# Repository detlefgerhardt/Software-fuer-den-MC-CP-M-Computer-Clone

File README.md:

# Software und Zubehör für den MC CP/M-Computer-Clone

**Dieses Repository befindet sich noch im Aufbau. Die Programme sind teilweise noch unvollständig und ungetestet!**

Dieses Repository enthält vollständig überarbeite Software (Monitor, BIOS und Tools) für den MC CP/M Computer Nachbau von Ulrich Haumann. Die Software basiert sowohl auf der Originalsoftware von Rolf-Dieter Klein als auch auf Änderungen und neuen Programmen von Ulrich Haumann.

**https://github.com/uli-pi/MC-CPM-Computer-Clone**

Zusätzlich findet man hier 3D-Druckteile und Adapter für den Einbau des Computers in ein 19" Systemgehäuse oder Baugruppenträger.

Ziel dieses Repositories hier ist es, die Software des MC CP/M Computer-Clones möglichst gut zu dokumentieren und weiter zu entwickeln.
Der Monitor soll kompatibel bleiben und die Kompatibilität des BIOS ist von CP/M vorgegeben. Teile des Monitors und des BIOS, die nicht für CP/M benötigt werden, wurden bereits weitgehend entfernt.

Geplante Erweiterungen:
- Optimierung, unnötige Routinen entfernen (im BIOS weitgehend erledigt, im Monitor ist noch einiges zu tun)
- Unterstützung weiterer Diskettenformate und eine einfacher Implementierung neuer Formate (weitgehend erledigt inkl. der dynmaischen Umkonfiguration der Laufwerksdaten zur Laufzweit (inzwischen implementiert und im Test)
- Die Hardwareunterstützung auf die aktuelle Hardware des MC CP/M-Clones reduzieren, um die Software zu vereinfachen. Wer erweiterte Kompatibilität benötigt, kann auf die Originalsoftware zurückgreifen).
- Unterstützung der IDE/CF-Karte gleichzeitig zusammen mit Diskettenlaufwerken (erledigt)
- Vereinheitlichung der Tools - zum Beispiel für die Nutzung von Disketten und IDE/CF-Laufwerke (hier kann noch weiter optimiert werden. Bisher gibt es noch eigene Tools zum Einrichten von IDE/CF-Laufwerken)

Dieses Repository enthält folgende Teilprojekte (noch in Arbeit, Liste nicht immer aktuell):
- **NMON** - der Monitor für den MC CP/M-Computer, geändert und erweitert, basierendem auf dem Original-Monitor von Rolf-Dieter Klein und einigen Anpassungen von Ulrich Haumann
- **NBIOS** - das angepasste BIOS, die Schnittstelle zwischen dem Monitor, der Hardware und CP/M (ebenfalls basierenden auf dem Original-BIOS von RDK)
- **NBIOS-CF** - angepasstes BIOS und Tools für das IDE/CF-Interface
- **NFORM** ist das originale in Z80 geschrieben Formatierprogramm für den MC CP/M-Computer. Da es lediglich den Monitor vorrausetzt, kann es ohne CP/M und BIOS direkt im Monitor ausgeführt werden.
- **MI-C** - in MI-C programmierte Programme und Tools, um Teil abgestimmt auf das NBIOS und nur mit diesem lauffähig
- **DEV-Tools** - Entwicklungstools für CP/M und Windows (Assembler, MI-C-Compiler, eigene Tools)
- **CPM-Standardsoftware** - Standard CP/M-Programme, die für Entwicklung und die Systemeinrichtung benötigt werde oder nützlich sind.
- **VT100-Animationen** - Ausgewählte VT100-Animationen inkl. Anzeige-Tools. Die Anzeige-Tools korrigieren nötigenfalls die Zeilenendezeichen und können auf Wunsch alle Dateien auf einem Laufwerk in zufälliger Reihenfolge ausgeben.

Zum Thema Gehäuse und 3D-Druck (neu):
- **Gehäuse und 3D-Druck** enthält Teile wie Fronplatten oder Laufwerkskäfige (Halterungen) für den Einbau in 19" Gehäuse und Baugruppenträger.
- **KiCAD** enthält derzeit Adapter-Platinen, die den Anschluss von Diskettenlaufwerken erleichtern.

Achtung. Die Versionierung und die Namen der Dateien wurden gegenüber den Originalen geändert, um eine klaren Schnitt zwischen der Originalsoftare und den Programmen dieses Projektes zu haben und Verwechselungen zu vermeiden.

Das CP/M wurde auf ein 58K-System geändert. Das CP/M beginnt bei Adresse CC00h und das BIOS bei Adresse E200h. Das war notwendig um ausreichend Platz für BIOS-Erweiterung, Debuggung und Experimente zu schaffen.

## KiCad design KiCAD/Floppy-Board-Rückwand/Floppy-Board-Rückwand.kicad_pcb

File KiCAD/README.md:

# Adapter-Platinen für den Gehäuseeinbau bzw. den einfacheren Anschluss von Laufwerken

* Der **MC_CPM_Floppyadapter** ist ein kleine Platine, mit dem man bis zu vier 3 1/2" Laufwerke ohne gedrehtes Kabel am FLO-Controller des MC CP/M-Computer betreiben kann. Auch gemischt mit 5 1/4" Laufwerken.

* **Floppy-Board-Rückwand** ist eine Platine, die den 34 und der 50-poligen Floppy-Anschluss auf der Rückseite eines Systemgehäuses herausführt. Ein passende Halterung findet man im Order 3D-Druck.

Bei Gelegenheit werde ich die Projekte umbenennen und sinnvolle Namen vergeben. ;-)

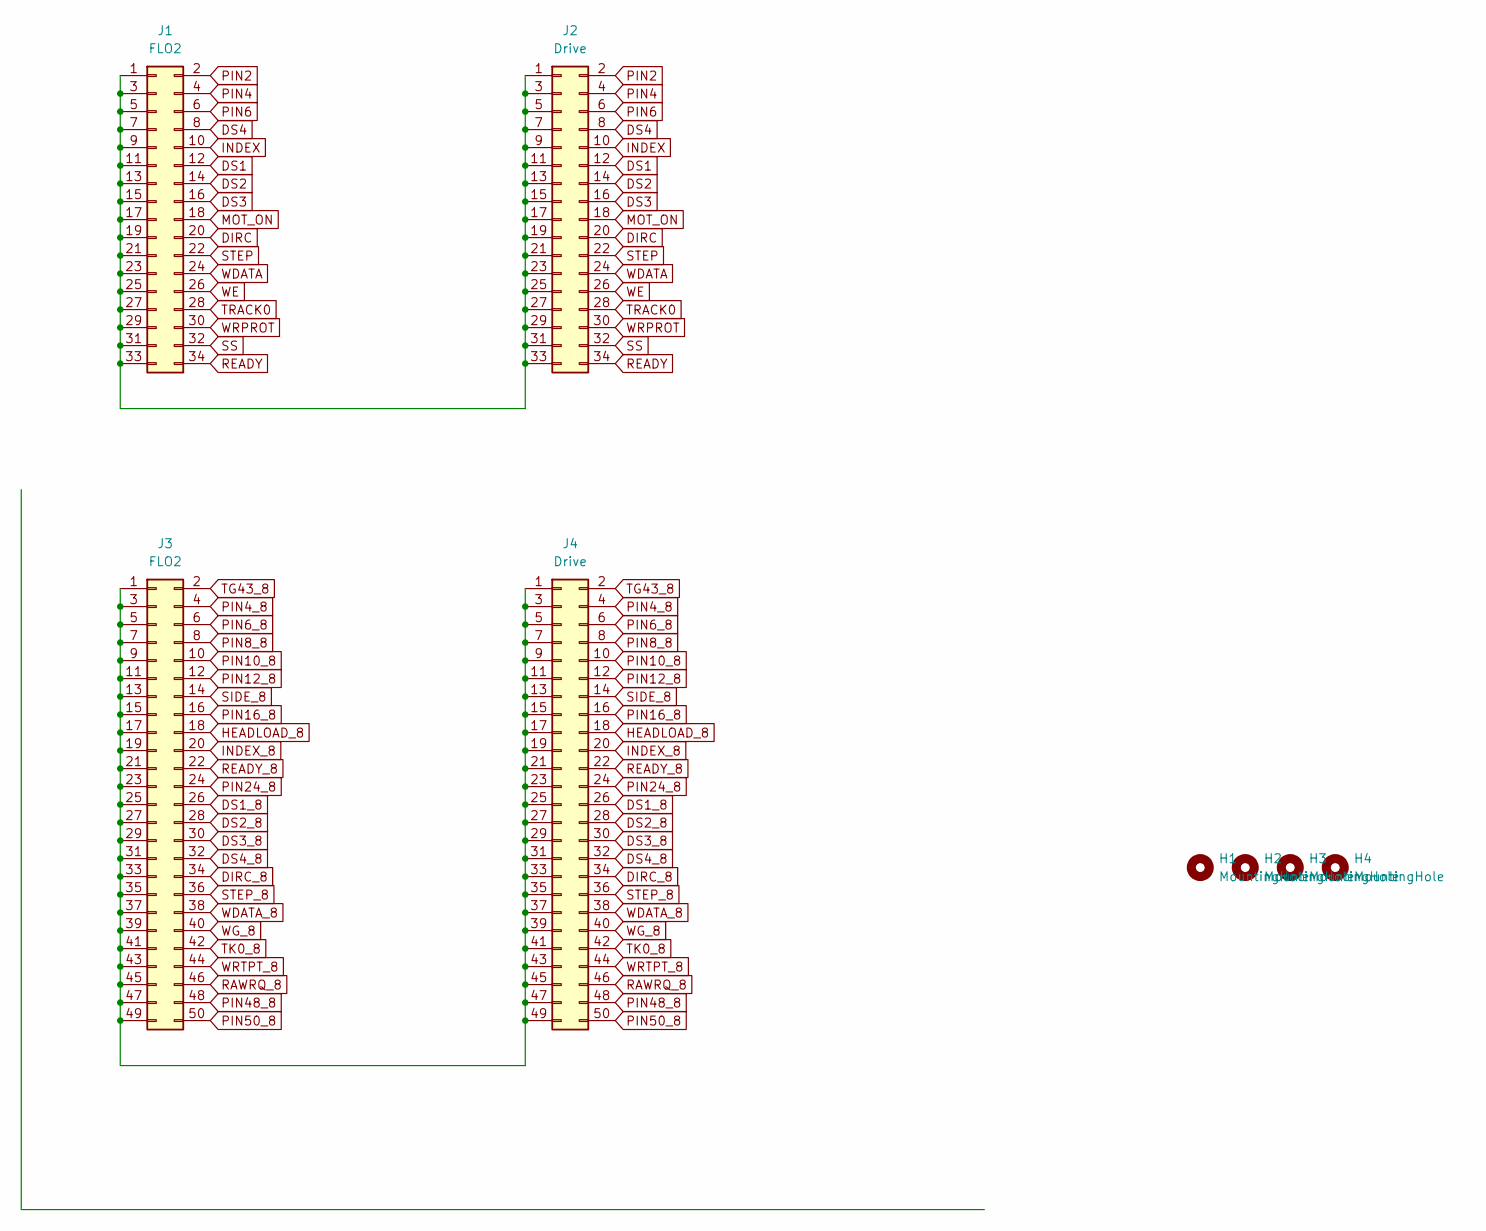
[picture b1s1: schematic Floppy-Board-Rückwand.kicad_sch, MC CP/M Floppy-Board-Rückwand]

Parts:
H1, H2, H3, H4: MountingHole; MountingHole_3.2mm_M3
J1: FLO2; PinSocket_2x17_P2.54mm_Vertical
J2: Drive; PinSocket_2x17_P2.54mm_Vertical
J3: FLO2; PinSocket_2x25_P2.54mm_Vertical
J4: Drive; PinSocket_2x25_P2.54mm_Vertical

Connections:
DIRC: J1.20, J2.20
DIRC_8: J3.34, J4.34
DS1: J1.12, J2.12
DS1_8: J3.26, J4.26
DS2: J1.14, J2.14
DS2_8: J3.28, J4.28
DS3: J1.16, J2.16
DS3_8: J3.30, J4.30
DS4: J1.8, J2.8
DS4_8: J3.32, J4.32
HEADLOAD_8: J3.18, J4.18
INDEX: J1.10, J2.10
INDEX_8: J3.20, J4.20
MOT_ON: J1.18, J2.18
unnamed: J1.1, J1.3, J1.5, J1.7, J1.9, J1.11, J1.13, J1.15, J1.17, J1.19, J1.21, J1.23, J1.25, J1.27, J1.29, J1.31, J1.33, J2.1, J2.3, J2.5, J2.7, J2.9, J2.11, J2.13, J2.15, J2.17, J2.19, J2.21, J2.23, J2.25, J2.27, J2.29, J2.31, J2.33
unnamed: J3.1, J3.3, J3.5, J3.7, J3.9, J3.11, J3.13, J3.15, J3.17, J3.19, J3.21, J3.23, J3.25, J3.27, J3.29, J3.31, J3.33, J3.35, J3.37, J3.39, J3.41, J3.43, J3.45, J3.47, J3.49, J4.1, J4.3, J4.5, J4.7, J4.9, J4.11, J4.13, J4.15, J4.17, J4.19, J4.21, J4.23, J4.25, J4.27, J4.29, J4.31, J4.33, J4.35, J4.37, J4.39, J4.41, J4.43, J4.45, J4.47, J4.49
PIN2: J1.2, J2.2
PIN4: J1.4, J2.4
PIN4_8: J3.4, J4.4
PIN6: J1.6, J2.6
PIN6_8: J3.6, J4.6
PIN8_8: J3.8, J4.8
PIN10_8: J3.10, J4.10
PIN12_8: J3.12, J4.12
PIN16_8: J3.16, J4.16
PIN24_8: J3.24, J4.24
PIN48_8: J3.48, J4.48
PIN50_8: J3.50, J4.50
RAWRQ_8: J3.46, J4.46
READY: J1.34, J2.34
READY_8: J3.22, J4.22
SIDE_8: J3.14, J4.14
SS: J1.32, J2.32
STEP: J1.22, J2.22
STEP_8: J3.36, J4.36
TG43_8: J3.2, J4.2
TK0_8: J3.42, J4.42
TRACK0: J1.28, J2.28
WDATA: J1.24, J2.24
WDATA_8: J3.38, J4.38
WE: J1.26, J2.26
WG_8: J3.40, J4.40
WRPROT: J1.30, J2.30
WRTPT_8: J3.44, J4.44

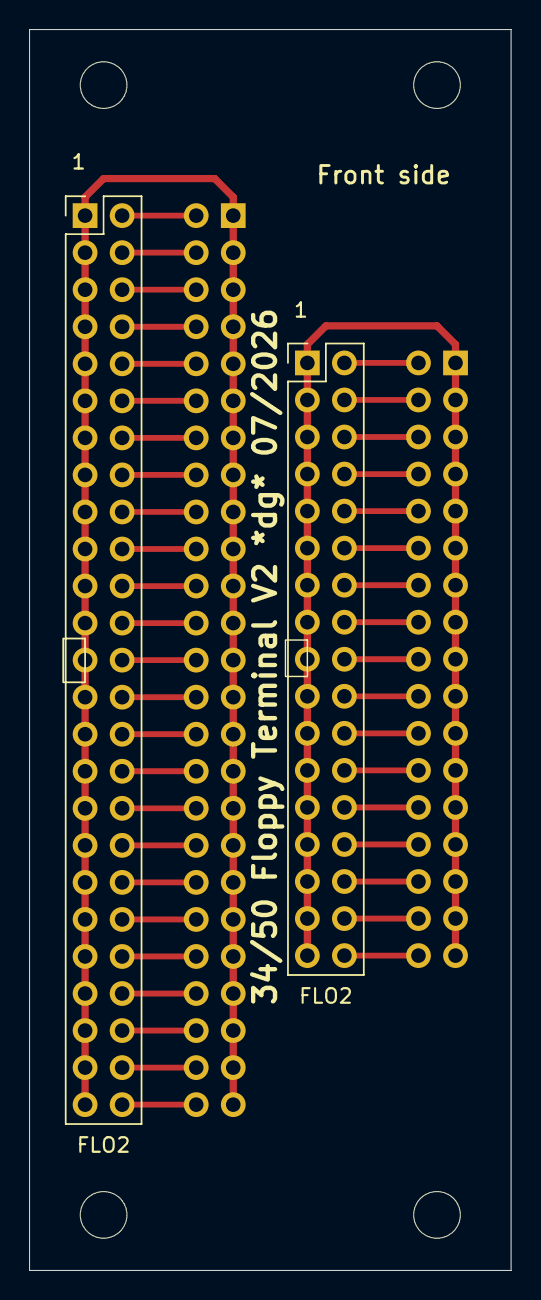
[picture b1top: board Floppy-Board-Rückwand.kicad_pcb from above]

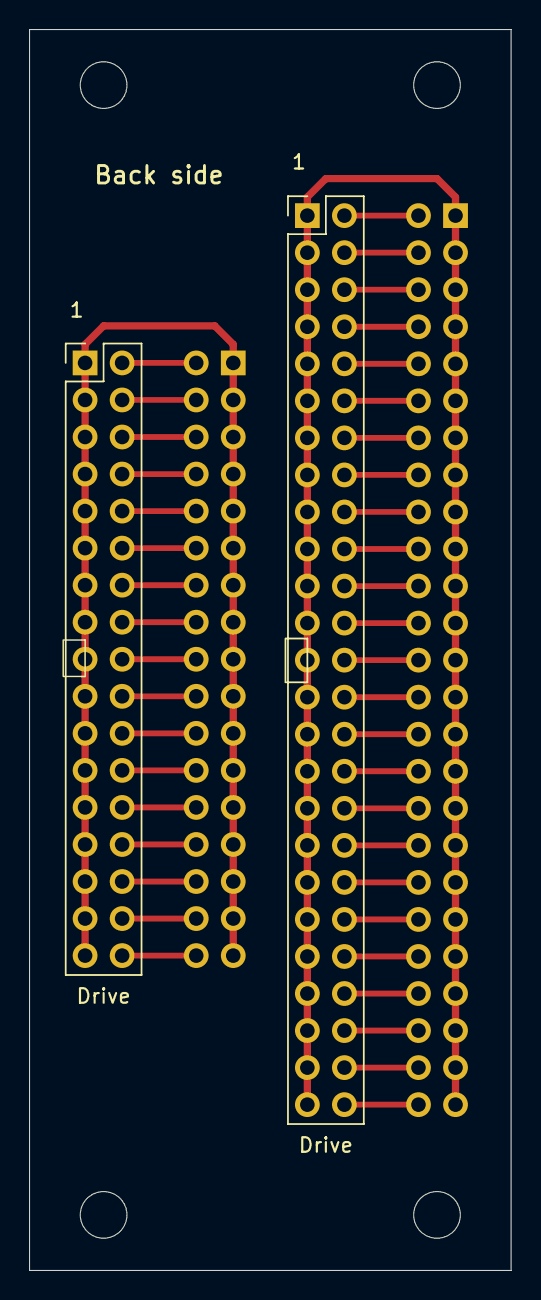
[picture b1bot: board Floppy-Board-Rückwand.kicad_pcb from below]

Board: 2 copper layers, 33.0 x 85.1 mm, 8 parts (2 on the bottom side), 44 nets.
